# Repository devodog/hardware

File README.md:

# hardware
This repository is to contain various hardware projects for PCB production using KiCad.

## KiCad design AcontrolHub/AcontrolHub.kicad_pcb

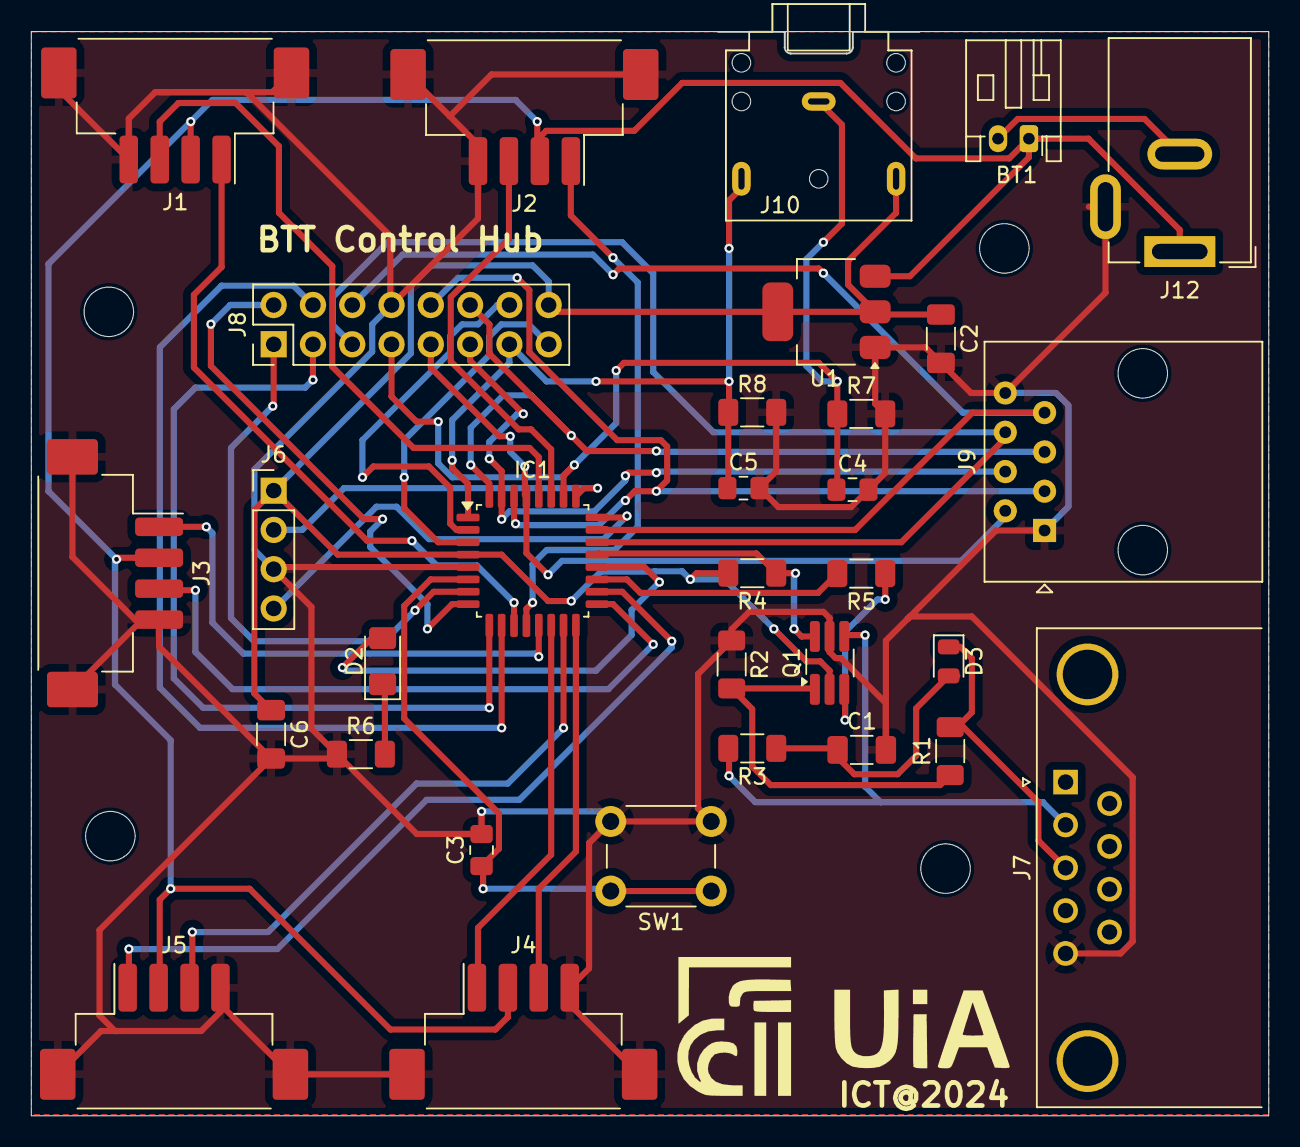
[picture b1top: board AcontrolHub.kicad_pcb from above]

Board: 2 copper layers, 79.9 x 70.0 mm, 32 parts (0 on the bottom side), 40 nets.

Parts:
BT1: Battery; JST_PH_S2B-PH-K_1x02_P2.00mm_Horizontal
C1: 47uF; C_1206_3216Metric_Pad1.33x1.80mm_HandSolder
C2: 470µ; C_1206_3216Metric_Pad1.33x1.80mm_HandSolder
C3, C4, C5: 100nF; C_0805_2012Metric_Pad1.18x1.45mm_HandSolder
C6: 100n; C_1206_3216Metric_Pad1.33x1.80mm_HandSolder
D2: LED; LED_1206_3216Metric_Pad1.42x1.75mm_HandSolder
D3: CD4148W; D_0805_2012Metric
IC1: STM32G030K6T6; LQFP-32_7x7mm_P0.8mm
J1: Target1; Hirose_DF3EA-04P-2H_1x04-1MP_P2.00mm_Horizontal
J2: Target2; Hirose_DF3EA-04P-2H_1x04-1MP_P2.00mm_Horizontal
J3: Target3; Hirose_DF3EA-04P-2H_1x04-1MP_P2.00mm_Horizontal
J4: Target4; Hirose_DF3EA-04P-2H_1x04-1MP_P2.00mm_Horizontal
J5: Target5; Hirose_DF3EA-04P-2H_1x04-1MP_P2.00mm_Horizontal
J6: SWD; PinHeader_1x04_P2.54mm_Vertical
J7: DB9_Female; DSUB-9_Female_Horizontal_P2.77x2.84mm_EdgePinOffset9.90mm_H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
J8: Utility Pins; PinHeader_2x08_P2.54mm_Vertical
J9: 8P8C; RJ45_Amphenol_54602-x08_Horizontal
J10: AudioJack3; Jack_3.5mm_CUI_SJ1-3523N_Horizontal
J12: Barrel_Jack_Switch; BarrelJack_GCT_DCJ200-10-A_Horizontal
Q1: FMB3946; TSOT-23-6_HandSoldering
R1, R2, R3, R4, R5, R7, R8: 10k; R_1206_3216Metric_Pad1.30x1.75mm_HandSolder
R6: 1k; R_1206_3216Metric_Pad1.30x1.75mm_HandSolder
SW1: RESET; SW_PUSH_6mm_H5mm
U1: AMS1117-3.3; SOT-223-3_TabPin2

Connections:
+6V: BT1.1 (+), J1.2, J2.2, J3.2, J4.2, J5.2, J12.1, U1.3 (VI)
GNDREF: C1.2, C2.2, C3.2, C4.2, C5.2, C6.2, IC1.5 (VSS/VSSA), J1.4, J1.MP, J2.4, J2.MP, J3.4, J3.MP, J4.4, J4.MP, J5.4, J5.MP, J6.3, J7.5, J8.8, J9.1, J9.8, J12.3, Q1.5 (E1), R2.1, R6.1, R7.2, R8.2, SW1.2, U1.1 (GND)
NRST: C3.1, IC1.6 (NRST), SW1.1
unnamed: BT1.2 (-), J12.2
unnamed: D2.2 (A), IC1.20 (PC6)
unnamed: D2.1 (K), R6.2
unnamed: C1.1, D3.2 (A), R3.1
unnamed: D3.1 (K), J7.3, R1.2
unnamed: C2.1, C6.1, IC1.4 (VDD/VDDA), J6.1, J8.16, J10.R, Q1.2 (E2), R4.2, U1.2 (VO)
unnamed: Q1.1 (B1), R1.1, R2.2
unnamed: Q1.3 (B2), R5.1
unnamed: J7.2, Q1.4 (C2), R3.2
PA0: IC1.7 (PA0), J8.1
PA1: IC1.8 (PA1), J8.2
PA11: IC1.22 (PA11), J8.5, J9.6
PA12: IC1.23 (PA12), J8.6, J9.7
PA15: C4.1, IC1.26 (PA15), J8.7, J10.S, R7.1
PB5: IC1.29 (PB5), J8.9, J9.2
PB6: IC1.30 (PB6), J8.10, J9.3
PB7: IC1.31 (PB7), J8.11, J9.4
PB8: IC1.32 (PB8), J8.12, J9.5
PB9: C5.1, IC1.1 (PB9), J8.13, J10.T, R8.1
PC14: IC1.2 (PC14-OSC32_IN), J8.14
PC15: IC1.3 (PC15-OSC32_OUT), J8.15
SWCLK/BOOT0: IC1.25 (PA14), J6.2
SWDIO: IC1.24 (PA13), J6.4
Servo1pwm: IC1.28 (PB4), J1.3
Servo2pwm: IC1.27 (PB3), J2.3
Servo3pwm: IC1.17 (PB2), J3.3
Servo4pwm: IC1.16 (PB1), J4.3
Servo5pwm: IC1.15 (PB0), J5.3
Target1int: IC1.11 (PA4), J1.1
Target2Int: IC1.12 (PA5), J2.1
Target3Int: IC1.13 (PA6), J3.1
Target4Int: IC1.14 (PA7), J4.1
Target5Int: IC1.18 (PA8), J5.1
USART1_RX: IC1.21 (PA10), Q1.6 (C1), R4.1
USART1_TX: IC1.19 (PA9), R5.2
USART2_RX: IC1.10 (PA3), J8.4
USART2_TX: IC1.9 (PA2), J8.3

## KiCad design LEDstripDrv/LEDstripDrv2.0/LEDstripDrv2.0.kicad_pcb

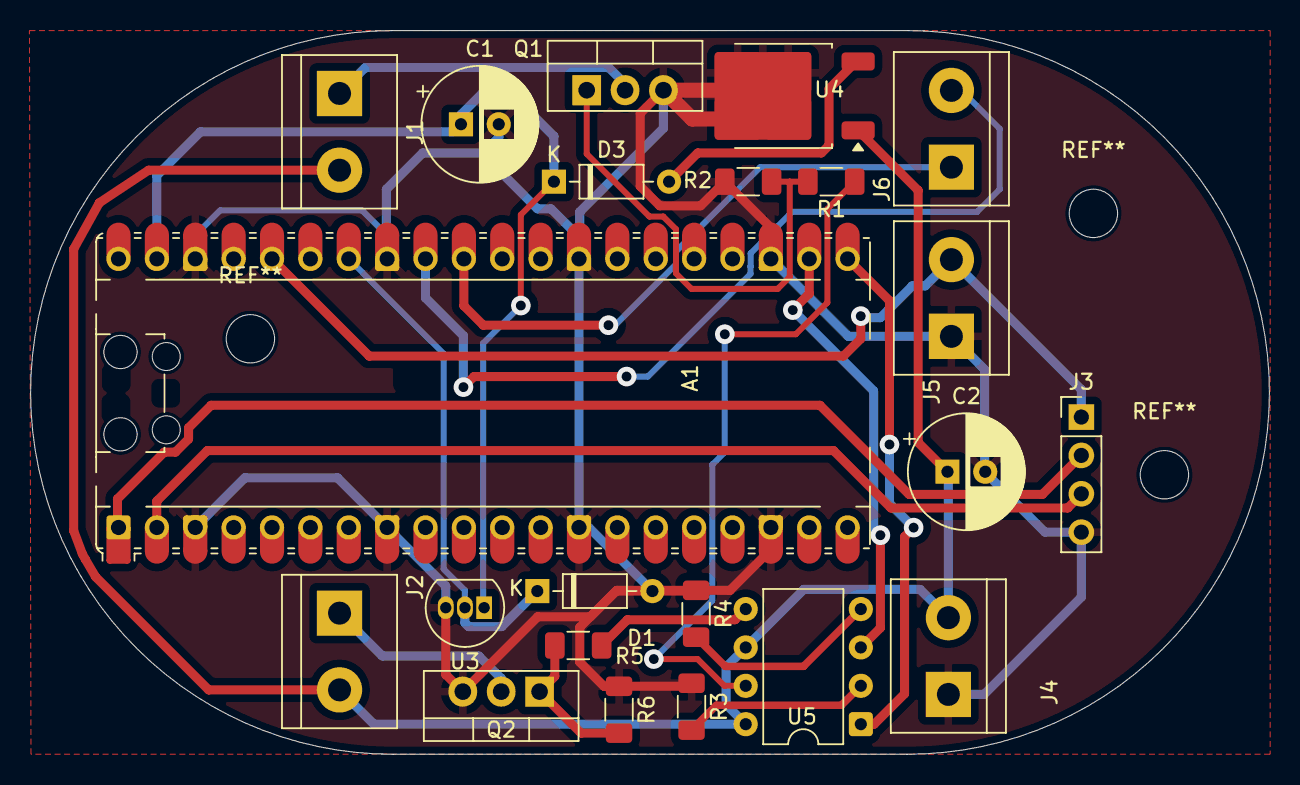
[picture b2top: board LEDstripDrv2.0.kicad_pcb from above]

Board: 2 copper layers, 82.0 x 47.9 mm, 22 parts (0 on the bottom side), 20 nets.

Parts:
A1: RaspberryPi_Pico; RaspberryPi_Pico_Common_Unspecified
C1: 100µF; CP_Radial_D7.5mm_P2.50mm
C2: 100µF30V; CP_Radial_D7.5mm_P2.50mm
D1: 3V; D_DO-35_SOD27_P7.62mm_Horizontal
D3: 1N4149; D_DO-35_SOD27_P7.62mm_Horizontal
J1, J2, J4, J5, J6: Screw_Terminal_01x02; TerminalBlock_bornier-2_P5.08mm
J3: Conn_01x04; PinHeader_1x04_P2.54mm_Vertical
Q1, Q2: IRF540N; TO-220-3_Vertical
R1, R5: 100; R_1206_3216Metric_Pad1.30x1.75mm_HandSolder
R2, R3, R4, R6: 1k; R_1206_3216Metric_Pad1.30x1.75mm_HandSolder
U3: LM35-LP; TO-92_Inline
U4: LF50_TO252; TO-252-2
U5: PC827; DIP-8_W7.62mm

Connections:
+24V: C2.1, J1.2, J2.2, J4.2, U4.1 (VI), U5.6, U5.8
GND: A1.3 (GND), A1.8 (GND), A1.13 (GND), A1.18 (GND), A1.23 (GND), A1.28 (GND), A1.33 (AGND), A1.38 (GND), C1.2, C2.2, D1.2 (A), J3.4, J4.1, J5.1, Q1.3 (S), Q2.3 (S), R2.1, R3.1, R4.1, R6.1, U3.3 (GND), U4.2 (GND)
unnamed: A1.36 (3V3), J3.1, J5.2
unnamed: A1.1 (GPIO0), J3.2
unnamed: A1.2 (GPIO1), J3.3
unnamed: A1.21 (GPIO16), U5.1
unnamed: A1.22 (GPIO17), U5.3
unnamed: A1.31 (GPIO26_ADC0), J6.1
unnamed: A1.32 (GPIO27_ADC1), J6.2
unnamed: A1.34 (GPIO28_ADC2), D1.1 (K), U3.2 (V_{OUT})
unnamed: A1.39 (VSYS), C1.1, D3.1 (K), U3.1 (+V_{S})
unnamed: D3.2 (A), U4.3 (VO)
unnamed: J1.1, Q1.2 (D)
unnamed: J2.1, Q2.2 (D)
unnamed: Q1.1 (G), R1.2, R2.2
unnamed: Q2.1 (G), R5.2, R6.2
unnamed: R1.1, U5.7
unnamed: R3.2, U5.2
unnamed: R4.2, U5.4
unnamed: R5.1, U5.5

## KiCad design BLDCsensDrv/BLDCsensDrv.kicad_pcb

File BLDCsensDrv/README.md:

# BLDC Driver for a bicycle motor
Schematics and PCB for a low voltage 3 phase MOSFET bridge driver

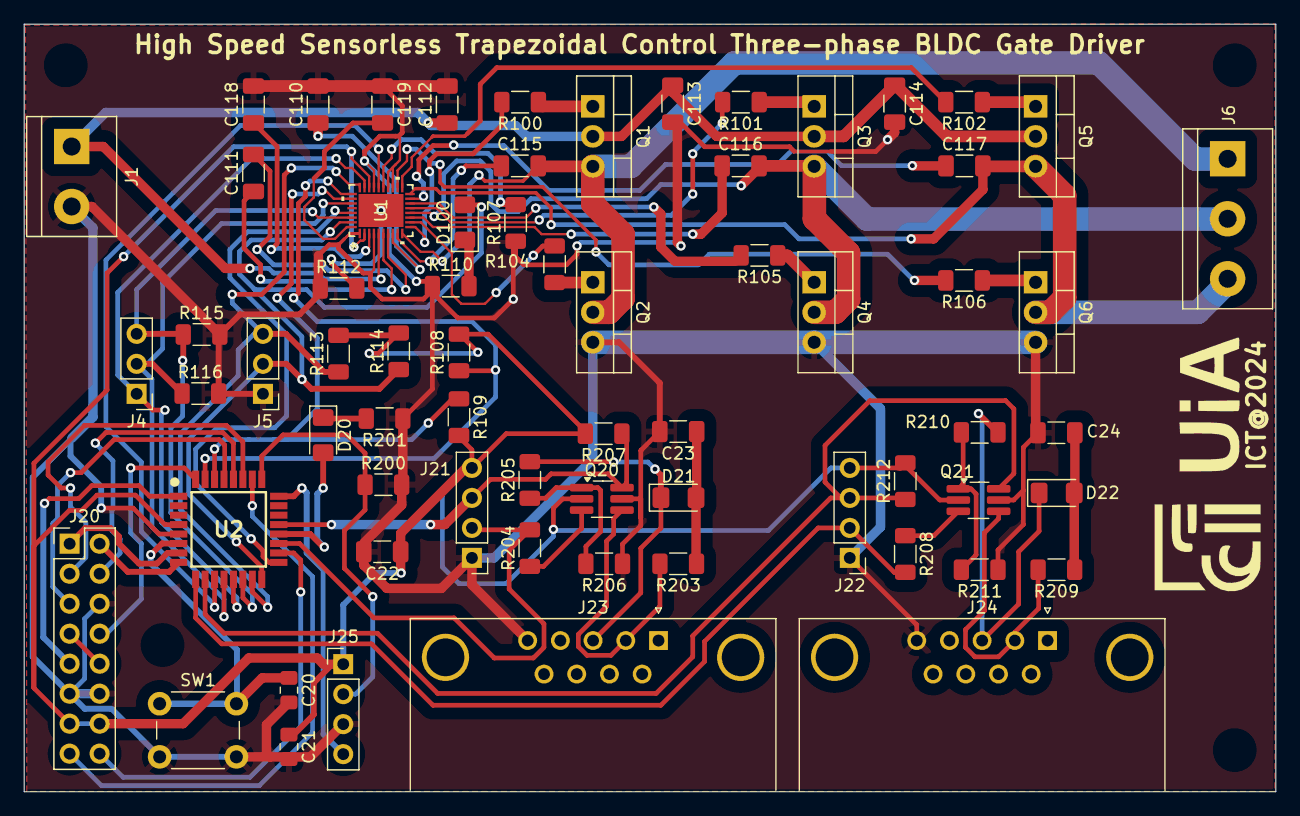
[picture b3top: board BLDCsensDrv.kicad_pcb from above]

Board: 2 copper layers, 106.0 x 65.0 mm, 67 parts (0 on the bottom side), 67 nets.

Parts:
C20, C21: 100nF; C_0805_2012Metric_Pad1.18x1.45mm_HandSolder
C22: 10uF; C_1206_3216Metric_Pad1.33x1.80mm_HandSolder
C23, C24: 47uF; C_1206_3216Metric_Pad1.33x1.80mm_HandSolder
C110: 10u; C_1206_3216Metric_Pad1.33x1.80mm_HandSolder
C111: 470n; C_1206_3216Metric_Pad1.33x1.80mm_HandSolder
C112, C113, C114: 100n; C_1206_3216Metric_Pad1.33x1.80mm_HandSolder
C115: 1µ; C_1206_3216Metric_Pad1.33x1.80mm_HandSolder
C116, C117, C119: 1u; C_1206_3216Metric_Pad1.33x1.80mm_HandSolder
C118: 2n; C_1206_3216Metric_Pad1.33x1.80mm_HandSolder
D20, D100: LED; LED_1206_3216Metric_Pad1.42x1.75mm_HandSolder
D21, D22: 1N4148; D_1206_3216Metric_Pad1.42x1.75mm_HandSolder
J1: Screw_Terminal_01x02; TerminalBlock_bornier-2_P5.08mm
J4: Ctrl-Port; PinHeader_1x03_P2.54mm_Vertical
J5: Monitor; PinHeader_1x03_P2.54mm_Vertical
J6: Screw_Terminal_01x03; TerminalBlock_bornier-3_P5.08mm
J20: Utility Pins; PinHeader_2x08_P2.54mm_Vertical
J21: UART PORT#1; PinHeader_1x04_P2.54mm_Vertical
J22: UART PORT#2; PinHeader_1x04_P2.54mm_Vertical
J23, J24: DB9_Female; DSUB-9_Female_Horizontal_P2.77x2.84mm_EdgePinOffset9.90mm_H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
J25: SWD; PinHeader_1x04_P2.54mm_Vertical
Q1, Q2, Q3, Q4, Q5, Q6: IRF540N; TO-220-3_Vertical
Q20, Q21: FMB3946; TSOT-23-6_HandSoldering
R100, R101, R102, R104, R105, R106: 15; R_1206_3216Metric_Pad1.30x1.75mm_HandSolder
R107: 0.1; R_1206_3216Metric_Pad1.30x1.75mm_HandSolder
R108, R109, R113, R114: 5.1k; R_1206_3216Metric_Pad1.30x1.75mm_HandSolder
R110, R201: 1k; R_1206_3216Metric_Pad1.30x1.75mm_HandSolder
R112: 0; R_1206_3216Metric_Pad1.30x1.75mm_HandSolder
R115, R116, R200, R203, R204, R205, R206, R207, R208, R209, R210, R211, R212: 10k; R_1206_3216Metric_Pad1.30x1.75mm_HandSolder
SW1: RESET; SW_PUSH_6mm_H5mm
U1: MCT8329A1IREER; WQFN36_REE_TEX
U2: STM32G030K6T6; QFP80P900X900X160-32N

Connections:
AGND: C20.2, C21.2, C22.2, C23.2, C24.2, C110.2, C112.2, C113.2, C114.2, C118.2, C119.1, J1.2, J5.1, J20.6, J20.11, J20.12, J21.1, J22.1, J23.5, J24.5, J25.3, Q2.3 (S), Q4.3 (S), Q6.3 (S), Q20.5 (E1), Q21.5 (E1), R107.1, R110.1, R112.1, R115.2, R116.2, R200.2, R201.1, R206.1, R211.1, SW1.2, U1.1 (DGND), U1.4 (GND), U1.21 (LSS), U1.22 (SP), U1.25 (AGND), U2.5 (VSS/VSSA)
AVDD: C21.1, C22.1, J20.13, J20.14, J21.4, J22.4, J25.1, Q20.2 (E2), Q21.2 (E2), R108.2, R109.2, R113.2, R114.2, R207.2, R212.2, U1.2 (VREG), U1.26 (AVDD), U2.4 (VDD/VDDA)
BRAKE: J4.3, R115.1, U1.34 (BRAKE), U2.14 (PA7)
DACOUT: U1.33 (DACOUT/SOX/SPEED_ANA), U2.17 (PB2)
DIR: J4.2, R116.1, U1.31 (DIR), U2.12 (PA5)
DRVOFF: U1.24 (DRVOFF), U2.11 (PA4)
FG: J5.3, R113.1, U1.28 (FG), U2.15 (PB0)
NFAULT: D100.2 (A), J5.2, R114.1, U1.35 (NFAULT), U2.16 (PB1)
NRST: C20.1, SW1.1, U2.6 (NRST)
unnamed: D20.2 (A), U2.20 (PC6)
unnamed: D20.1 (K), R201.2
unnamed: C23.1, D21.2 (A), R203.1
unnamed: D21.1 (K), J23.3, R205.2
unnamed: C24.1, D22.2 (A), R209.1
unnamed: D22.1 (K), J24.3, R210.2
unnamed: D100.1 (K), R110.2
unnamed: C115.2, J6.1, Q1.3 (S), Q2.2 (D), U1.10 (SHA)
unnamed: C116.2, J6.2, Q3.3 (S), Q4.2 (D), U1.14 (SHB)
unnamed: C117.2, J6.3, Q5.3 (S), Q6.2 (D), U1.18 (SHC)
unnamed: J20.7, J20.10
unnamed: Q1.1 (G), R100.1
unnamed: Q2.1 (G), R104.1
unnamed: Q3.1 (G), R101.1
unnamed: Q4.1 (G), R105.1
unnamed: Q5.1 (G), R102.1
unnamed: Q6.1 (G), R106.1
unnamed: Q20.1 (B1), R205.1, R206.2
unnamed: Q20.3 (B2), R204.1
unnamed: J23.2, Q20.4 (C2), R203.2
unnamed: Q21.1 (B1), R210.1, R211.2
unnamed: Q21.3 (B2), R208.1
unnamed: J24.2, Q21.4 (C2), R209.2
unnamed: C115.1, U1.9 (BSTA)
unnamed: C116.1, U1.13 (BSTB)
unnamed: C117.1, U1.17 (BSTC)
unnamed: C111.2, U1.7 (CPH)
unnamed: C111.1, U1.6 (CPL)
unnamed: C119.2, U1.36 (DVDD)
unnamed: R112.2, U1.37 (EPAD)
unnamed: C118.1, U1.3 (GCTRL)
unnamed: R100.2, U1.11 (GHA)
unnamed: R101.2, U1.15 (GHB)
unnamed: R102.2, U1.19 (GHC)
unnamed: R104.2, U1.12 (GLA)
unnamed: R105.2, U1.16 (GLB)
unnamed: R106.2, U1.20 (GLC)
unnamed: C110.1, U1.8 (GVDD)
unnamed: R107.2, U1.23 (SN)
PA0: J20.1, U2.7 (PA0)
PA1: J20.2, U2.8 (PA1)
PA8: J20.16, U2.18 (PA8)
PA15: J20.15, U2.26 (PA15)
PB3: J20.3, U2.27 (PB3)
PB4: J20.4, U2.28 (PB4)
PB5: J20.5, U2.29 (PB5)
PB8: J20.8, U2.32 (PB8)
PB9: J20.9, U2.1 (PB9)
PVDD: C112.1, C113.1, C114.1, J1.1, Q1.2 (D), Q3.2 (D), Q5.2 (D), U1.5 (PVDD)
SCL: R109.1, U1.30 (SCL), U2.30 (PB6)
SDA: R108.1, U1.29 (SDA), U2.31 (PB7)
SPEED/_WAKE: J4.1, U1.27 (SPEED/_WAKE), U2.13 (PA6)
SWCLK/BOOT0: J25.2, R200.1, U2.25 (PA14)
SWDIO: J25.4, U2.24 (PA13)
USART1_RX: J21.3, Q20.6 (C1), R207.1, U2.21 (PA10)
USART1_TX: J21.2, R204.2, U2.19 (PA9)
USART2_RX: J22.3, Q21.6 (C1), R212.1, U2.10 (PA3)
USART2_TX: J22.2, R208.2, U2.9 (PA2)

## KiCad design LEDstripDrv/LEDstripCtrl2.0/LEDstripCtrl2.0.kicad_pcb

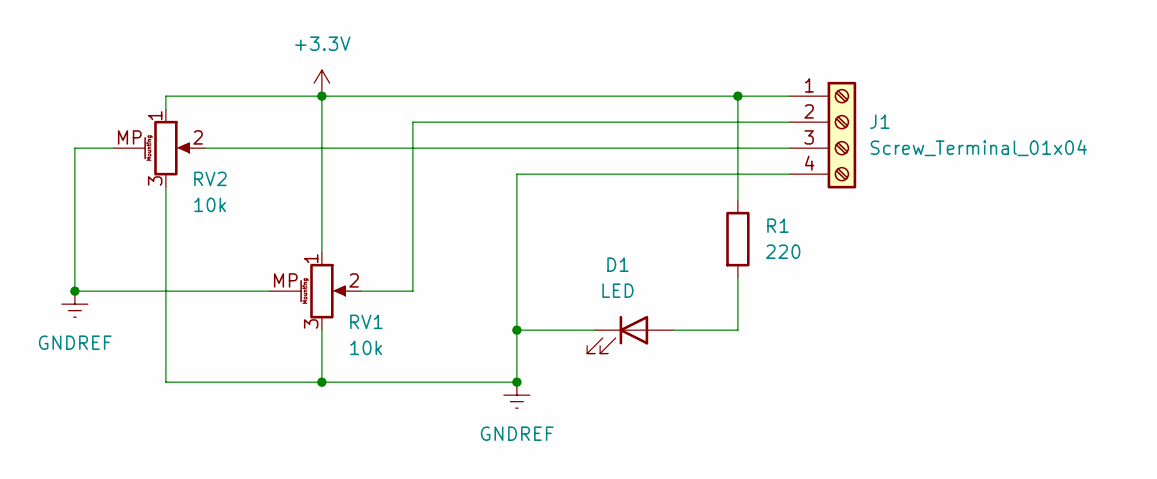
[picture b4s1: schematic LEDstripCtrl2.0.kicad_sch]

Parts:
D1: LED; LED_D3.0mm
J1: Screw_Terminal_01x04; TerminalBlock_Phoenix_MKDS-1,5-4-5.08_1x04_P5.08mm_Horizont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
R1: 220; R_Axial_DIN0309_L9.0mm_D3.2mm_P12.70mm_Horizontal
RV1, RV2: 10k; Potentiometer_Bourns_PTA4543_Single_Slide

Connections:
+3.3V: J1.1, R1.1, RV1.1, RV2.1
GNDREF: D1.1 (K), J1.4, RV1.3, RV1.MP (MountPin), RV2.3, RV2.MP (MountPin)
unnamed: D1.2 (A), R1.2
unnamed: J1.2, RV1.2
unnamed: J1.3, RV2.2

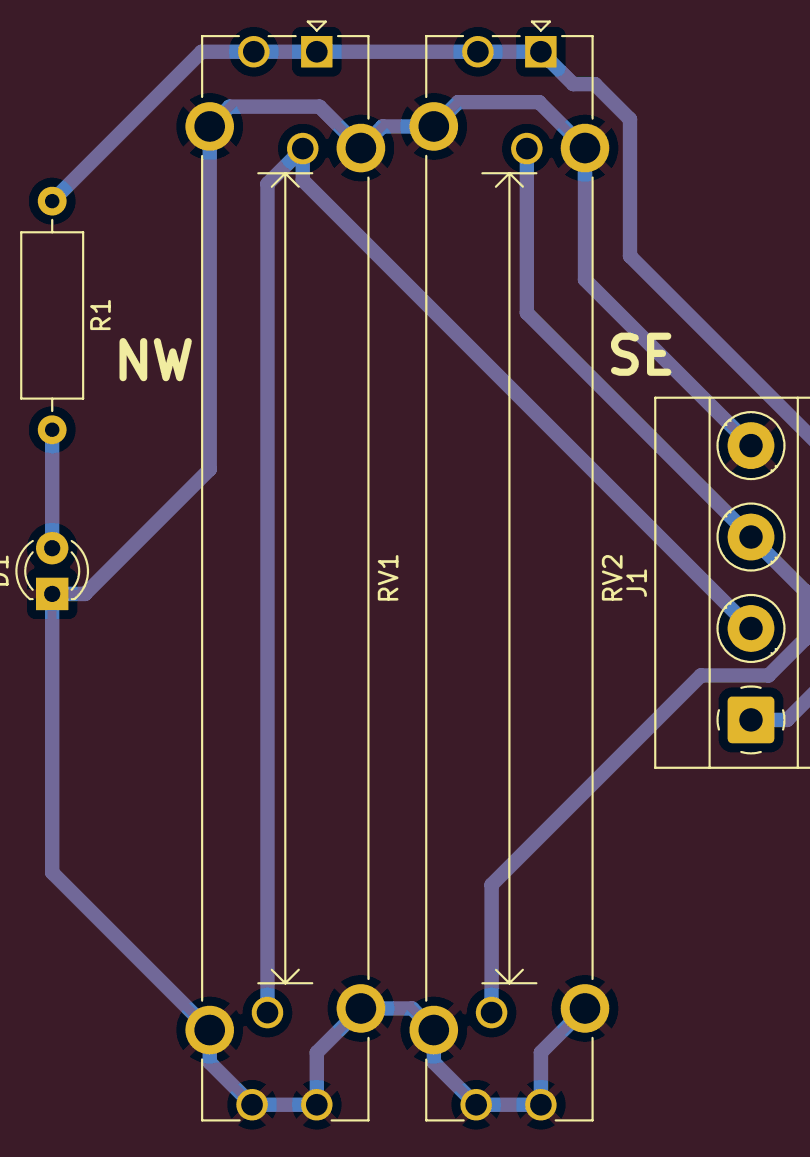
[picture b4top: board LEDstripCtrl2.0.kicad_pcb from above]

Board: 2 copper layers, 5 parts (0 on the bottom side), 5 nets.

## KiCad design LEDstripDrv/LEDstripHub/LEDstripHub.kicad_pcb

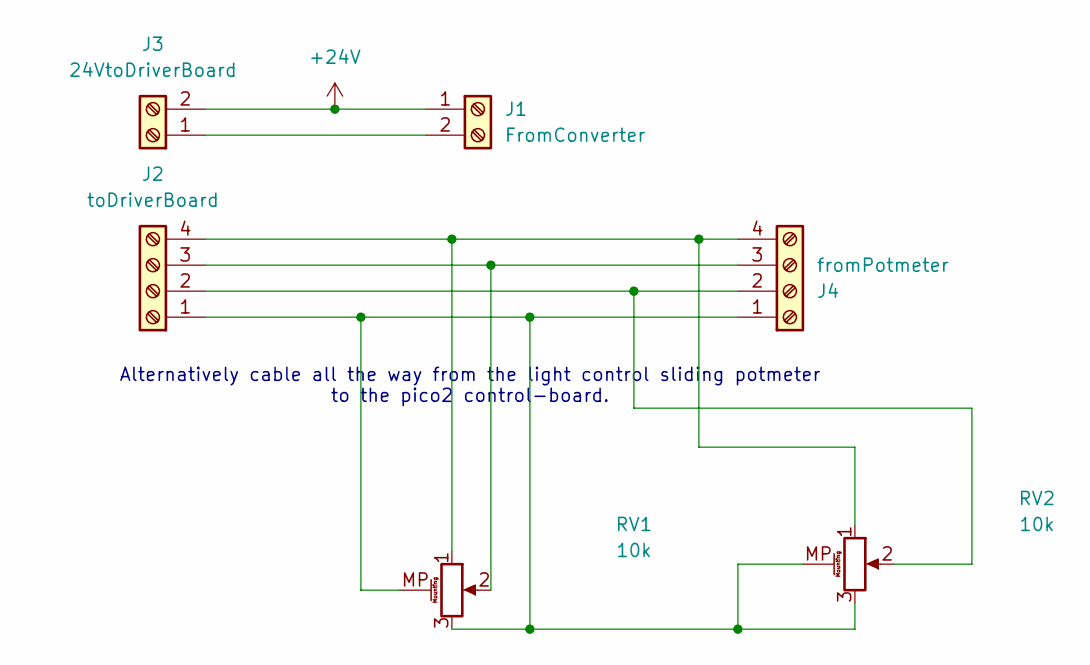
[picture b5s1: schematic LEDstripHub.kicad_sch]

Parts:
J1: FromConverter; TerminalBlock_Phoenix_MKDS-1,5-2-5.08_1x02_P5.08mm_Horizont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
J2: toDriverBoard; TerminalBlock_Phoenix_MKDS-1,5-4-5.08_1x04_P5.08mm_Horizont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
J3: 24VtoDriverBoard; TerminalBlock_Phoenix_MKDS-1,5-2-5.08_1x02_P5.08mm_Horizont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
J4: fromPotmeter; TerminalBlock_Phoenix_MKDS-1,5-4-5.08_1x04_P5.08mm_Horizont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
RV1, RV2: 10k; Potentiometer_Bourns_PTA4543_Single_Slide

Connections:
+24V: J1.1, J3.2
unnamed: J1.2, J3.1
unnamed: J2.1, J4.1, RV1.3, RV1.MP (MountPin), RV2.3, RV2.MP (MountPin)
unnamed: J2.2, J4.2, RV2.2
unnamed: J2.3, J4.3, RV1.2
unnamed: J2.4, J4.4, RV1.1, RV2.1

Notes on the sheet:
Alternatively cable all the way from the light control sliding potmeter to the pico2 control-board.

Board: 2 copper layers, 6 parts (0 on the bottom side), 6 nets, no tracks yet.

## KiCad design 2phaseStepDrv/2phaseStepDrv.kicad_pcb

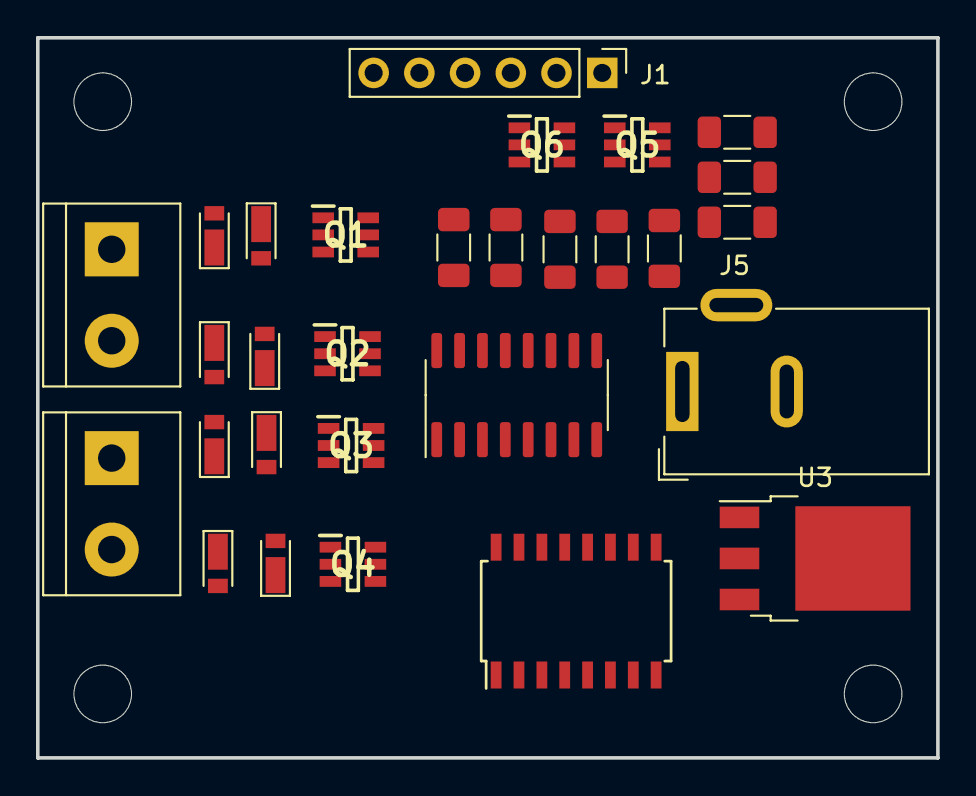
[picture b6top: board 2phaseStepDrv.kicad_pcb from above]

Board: 2 copper layers, 50.0 x 40.0 mm, 33 parts (0 on the bottom side), 31 nets, no tracks yet.

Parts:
D1, D2, D3, D4, D5, D6, D7, D8: 1N4149; D_TUMD2
H1, H2, H3, H4: MountingHole; MountingHole_3.2mm_M3
J1: mcu intf; PinHeader_1x06_P2.54mm_Vertical
J2: Phase-A; TerminalBlock_bornier-2_P5.08mm
J3: Phase-B; TerminalBlock_bornier-2_P5.08mm
J5: 12V input; BarrelJack_Wuerth_6941xx301002
Q1, Q2, Q3, Q4, Q5, Q6: FMBM5551; SOT95P280X110-6N
R1, R2, R3, R4, R5, R6, R7, R8: 10k; R_1206_3216Metric_Pad1.30x1.75mm_HandSolder
RN1: R_Pack08; SOIC-16W_5.3x10.2mm_P1.27mm
U1: 4028; SOIC-16_3.9x9.9mm_P1.27mm
U3: L7805; TO-252-3_TabPin2

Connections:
+12V: D1.1 (K), D3.1 (K), D5.1 (K), D7.1 (K), J5.1, Q1.6 (C1), Q2.6 (C1), Q3.6 (C1), Q4.6 (C1), R1.1, R2.1, R3.1, R4.1, U1.16 (VDD), U3.1 (IN)
Earth: D2.2 (A), D4.2 (A), D6.2 (A), D8.2 (A), J1.6, J5.2, J5.3, Q1.2 (E2), Q2.2 (E2), Q3.2 (E2), Q4.2 (E2), Q5.2 (E2), Q5.5 (E1), Q6.2 (E2), Q6.5 (E1), U1.8 (VSS), U3.2 (GND)
unnamed: D1.2 (A), D2.1 (K), J2.1, Q1.4 (C2), Q1.5 (E1)
unnamed: D3.2 (A), D4.1 (K), J2.2, Q2.4 (C2), Q2.5 (E1)
unnamed: D5.2 (A), D6.1 (K), J3.1, Q3.4 (C2), Q3.5 (E1)
unnamed: D7.2 (A), D8.1 (K), J3.2, Q4.4 (C2), Q4.5 (E1)
unnamed: J1.1, R5.2
unnamed: J1.2, R6.2
unnamed: J1.3, R7.2
unnamed: J1.4, R8.2
unnamed: J1.5, U3.3 (OUT)
unnamed: Q1.1 (B1), RN1.8 (R8.1)
unnamed: Q1.3 (B2), RN1.5 (R5.1)
unnamed: Q2.1 (B1), RN1.7 (R7.1)
unnamed: Q2.3 (B2), RN1.6 (R6.1)
unnamed: Q3.1 (B1), RN1.4 (R4.1)
unnamed: Q3.3 (B2), RN1.1 (R1.1)
unnamed: Q4.1 (B1), RN1.2 (R2.1)
unnamed: Q4.3 (B2), RN1.3 (R3.1)
unnamed: Q5.1 (B1), R5.1
unnamed: Q5.3 (B2), R6.1
unnamed: Q5.6 (C1), R1.2, U1.10 (A)
unnamed: Q5.4 (C2), R2.2, U1.13 (B)
unnamed: Q6.1 (B1), R7.1
unnamed: Q6.3 (B2), R8.1
unnamed: Q6.6 (C1), R3.2, U1.12 (C)
unnamed: Q6.4 (C2), R4.2, U1.11 (D)
unnamed: RN1.15 (R2.2), RN1.16 (R1.2), U1.15 (S3)
unnamed: RN1.13 (R4.2), RN1.14 (R3.2), U1.2 (S2)
unnamed: RN1.11 (R6.2), RN1.12 (R5.2), U1.14 (S1)
unnamed: RN1.9 (R8.2), RN1.10 (R7.2), U1.3 (S0)

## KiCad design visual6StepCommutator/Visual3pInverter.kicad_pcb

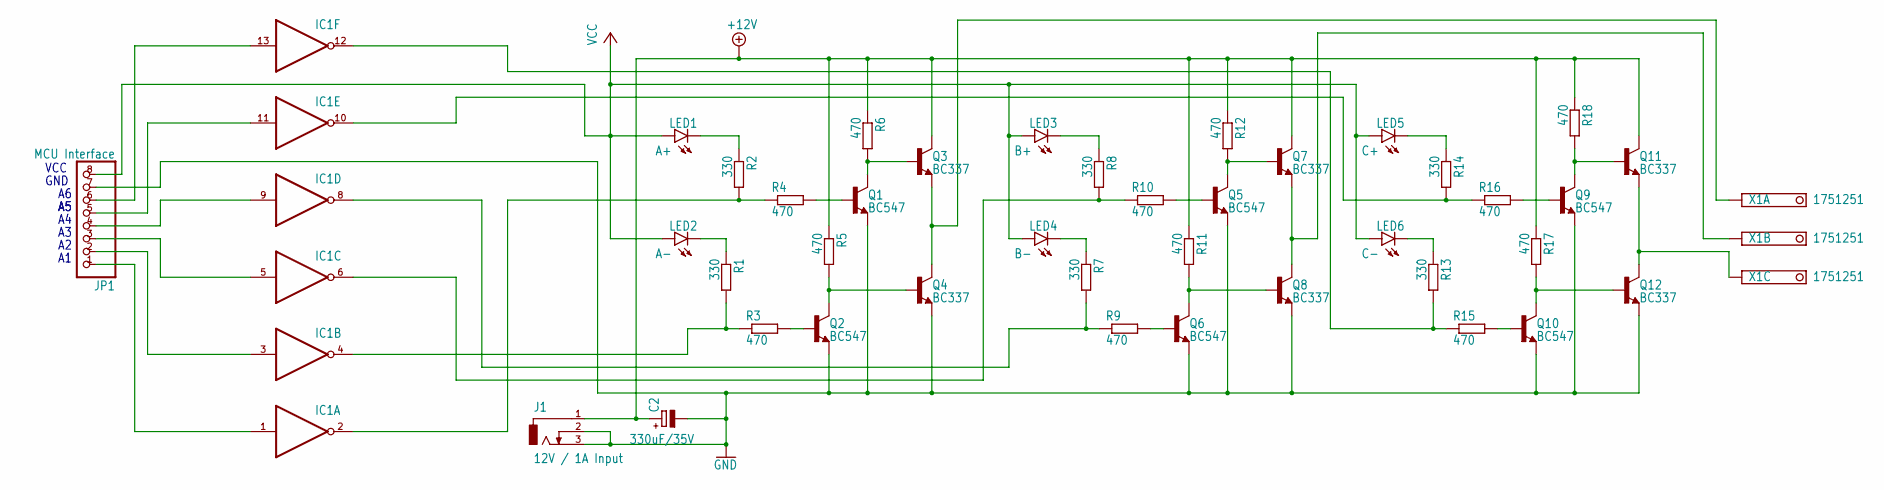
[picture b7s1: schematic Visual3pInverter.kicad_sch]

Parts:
C2: 330uF/35V; E5-10,5
IC1: 7404N; DIL14
J1: 12V / 1A Input; DCJ0303
JP1: MCU Interface; 1X08
LED1: A+; LED3MM
LED2: A-; LED3MM
LED3: B+; LED3MM
LED4: B-; LED3MM
LED5: C+; LED3MM
LED6: C-; LED3MM
Q1, Q2, Q5, Q6, Q9, Q10: BC547; TO92
Q3, Q4, Q7, Q8, Q11, Q12: BC337; TO92
R1, R2, R7, R8, R13, R14: 330; 0204_7
R3, R4, R5, R6, R9, R10, R11, R12, R15, R16, R17, R18: 470; 0204_7
X1: 1751251

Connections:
+12V: C2.+, J1.1, Q3.3 (C), Q7.3 (C), Q11.3 (C), R5.1, R6.1, R11.1, R12.1, R17.1, R18.1
GND: C2.-, J1.2, J1.3, JP1.7, Q1.1 (E), Q2.1 (E), Q4.1 (E), Q5.1 (E), Q6.1 (E), Q8.1 (E), Q9.1 (E), Q10.1 (E), Q12.1 (E)
unnamed: IC1.1 (I), JP1.1
unnamed: IC1.2 (O), R2.2, R4.1
unnamed: IC1.3 (I), JP1.2
unnamed: IC1.4 (O), R1.2, R3.1
unnamed: IC1.5 (I), JP1.3
unnamed: IC1.6 (O), R8.2, R10.1
unnamed: IC1.9 (I), JP1.4
unnamed: IC1.8 (O), R7.2, R9.1
unnamed: IC1.11 (I), JP1.5
unnamed: IC1.10 (O), R14.2, R16.1
unnamed: IC1.13 (I), JP1.6
unnamed: IC1.12 (O), R13.2, R15.1
unnamed: LED1.K (C), R2.1
unnamed: LED2.K (C), R1.1
unnamed: LED3.K (C), R8.1
unnamed: LED4.K (C), R7.1
unnamed: LED5.K (C), R14.1
unnamed: LED6.K (C), R13.1
unnamed: Q1.2 (B), R4.2
unnamed: Q1.3 (C), Q3.2 (B), R6.2
unnamed: Q2.2 (B), R3.2
unnamed: Q2.3 (C), Q4.2 (B), R5.2
unnamed: Q3.1 (E), Q4.3 (C), X1.1 (K)
unnamed: Q5.2 (B), R10.2
unnamed: Q5.3 (C), Q7.2 (B), R12.2
unnamed: Q6.2 (B), R9.2
unnamed: Q6.3 (C), Q8.2 (B), R11.2
unnamed: Q7.1 (E), Q8.3 (C), X1.2 (K)
unnamed: Q9.2 (B), R16.2
unnamed: Q10.2 (B), R15.2
unnamed: Q10.3 (C), Q12.2 (B), R17.2
unnamed: Q9.3 (C), Q11.2 (B), R18.2
unnamed: Q11.1 (E), Q12.3 (C), X1.3 (K)
VCC: JP1.8, LED1.A, LED2.A, LED3.A, LED4.A, LED5.A, LED6.A

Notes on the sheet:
GND
VCC

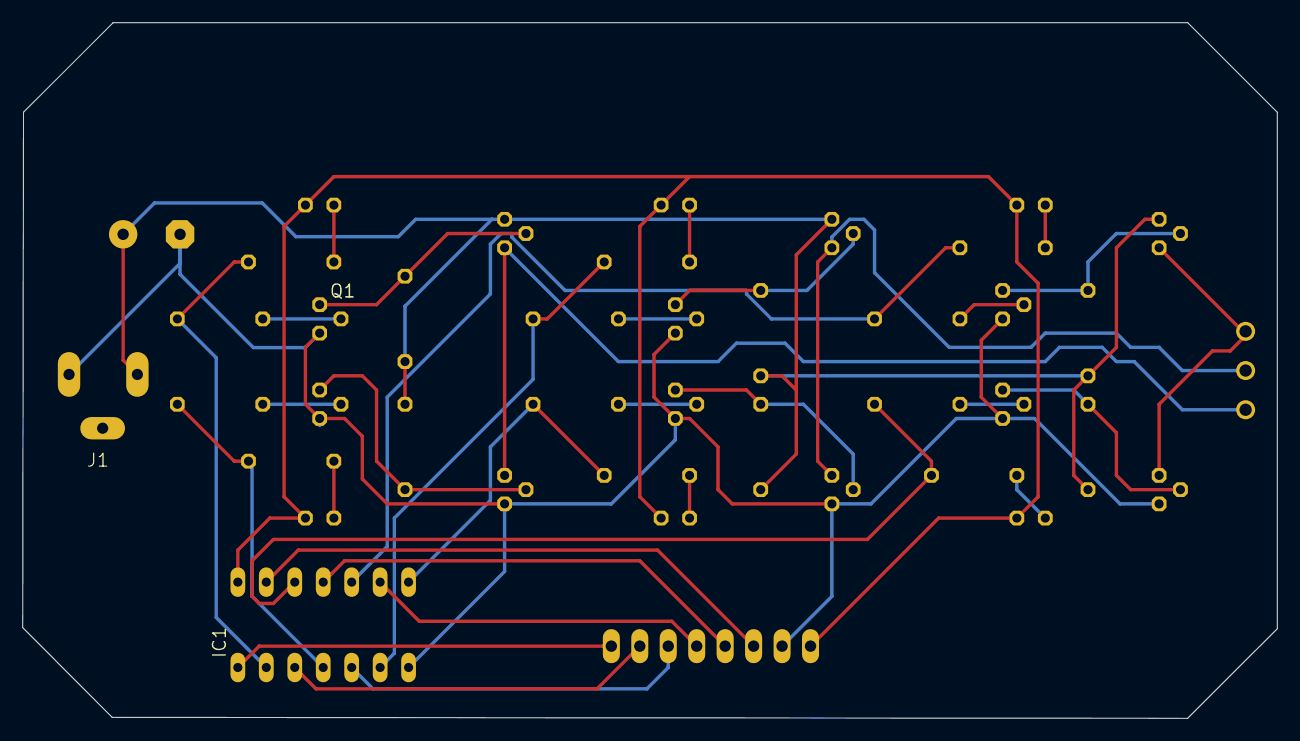
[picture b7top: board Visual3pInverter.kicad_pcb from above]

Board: 2 copper layers, 112.0 x 62.1 mm, 41 parts (0 on the bottom side), 36 nets.

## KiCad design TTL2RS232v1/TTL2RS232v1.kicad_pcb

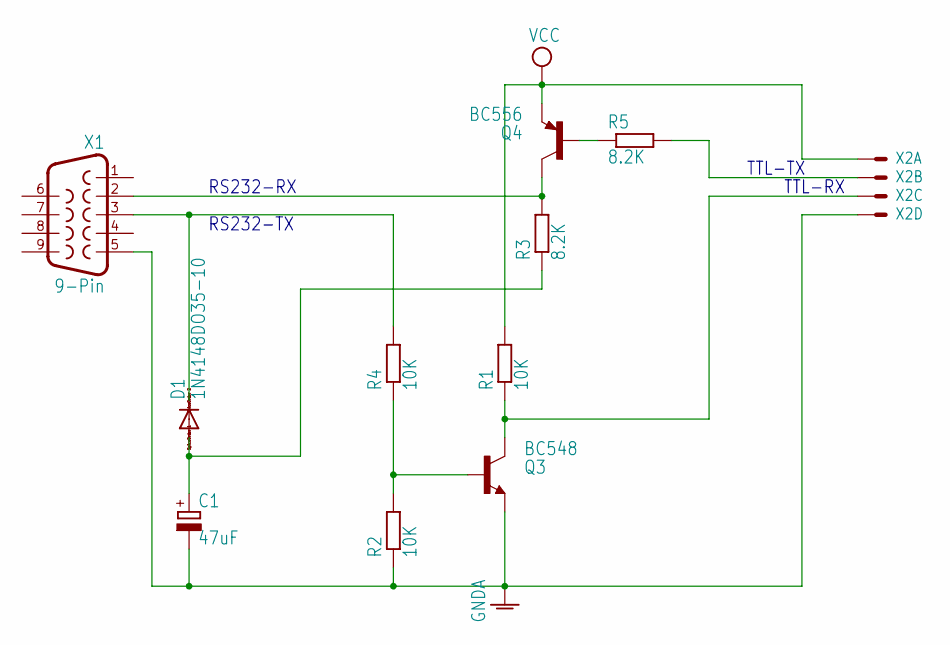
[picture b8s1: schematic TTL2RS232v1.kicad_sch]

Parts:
C1: 47uF; E2,5-7
D1: 1N4148DO35-10; DO35-10
Q3: BC548; TO92-EBC
Q4: BC556; TO92-EBC
R1, R2, R4: 10K; 0207_10
R3, R5: 8.2K; 0207_10
X1: 9-Pin; F09H
X2: 22-23-2041

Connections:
GNDA: C1.-, Q3.E, R2.1, X1.5, X2.4
unnamed: Q3.C, R1.1, X2.3
unnamed: Q3.B, R2.2, R4.1
unnamed: C1.+, D1.A, R3.1
unnamed: D1.C, R4.2, X1.3
unnamed: Q4.C, R3.2, X1.2
unnamed: Q4.B, R5.1
unnamed: R5.2, X2.2
VCC: Q4.E, R1.2, X2.1

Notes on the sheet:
TTL-RX
RS232-TX
RS232-RX
TTL-TX

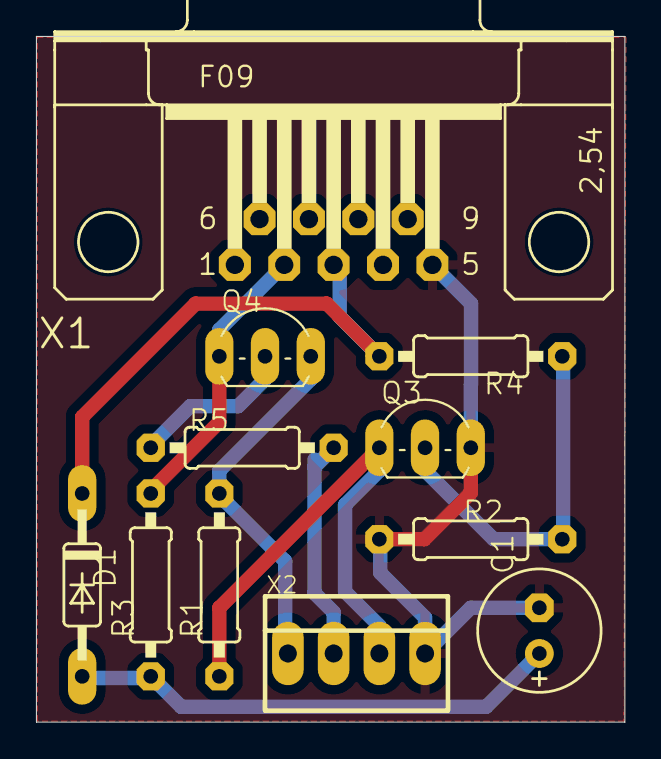
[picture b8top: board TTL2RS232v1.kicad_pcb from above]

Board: 2 copper layers, 32.7 x 38.1 mm, 11 parts (0 on the bottom side), 9 nets.

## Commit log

2024-03-23 First version for PCB production.
2024-03-28 Initial bldc hardware included in this repository
2024-04-05 Production ready pcb
2024-04-05 3D model for casing the Big7segDisplayDrv hardware
2024-04-18 Updating the list of kicad backup-files
2024-04-18 J4 header orientation changed, mount holes added and additinal AGND fill
2024-04-18 Gerber-files of current date
2024-04-18 3D sketchup files update for hardware casing
2024-04-18 Latest design backup files
2024-04-18 Commiting latest work on this project - not completed.
2024-04-18 General development update including aditional data sheet
2024-04-18 Update wire width, mount holes and silkprint info
2024-05-16 Simple six-step commutator with 5V LDO ready for prototype prod.
2024-05-16 3-phase Trapezoidal Control hardware ready for prototype prod.
2024-05-16 Big7segDisplay prototype prod. completed.
2024-05-16 backup commited
2024-05-29 Biathlon Toy Target included in the hardware repository - PCB-0 ordered
2024-05-29 Including gerberfiles for the first PCB prod.
2024-05-29 Schematic update.
2024-08-16 New board for mandatory lab-work for ELE302 course in wireless access.
2025-06-20 First design of Water Level Indicator.
2025-06-20 Removed old back-ups.
2025-06-20 Last years (2024) ELE302 lab project.
2025-06-20 Checking in the current design and prod files.
2025-06-20 Checking in current design and production files.
2025-07-15 Hasty checkin of current development projects...
